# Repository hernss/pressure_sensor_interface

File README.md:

# Descripción del proyecto:

Se desea realizar un dispositivo que sirva de interface para un sensor analógico de presión. El sensor en cuestión es un sensor de presión absoluta que trabaja sobre una línea de aire comprimido, la salida de dicho sensor es del tipo 4-20mA y el rango te trabajo es de 0 a 10bar.
Este dispositivo tiene como objetivo mantener la línea de aire comprimido en un rango de presión predefinido por el usuario, y en caso de no encontrarse en dicho límite actúa como dispositivo de seguridad liberando la presión en la línea y haciendo sonar una alarma.
El núcleo de este proyecto es un Cortex M3 de la familia de STM el cual lleva implementado un sistema de control del estilo TDS el cual nos asegura el tiempo de respuesta en caso de presentarse una falla.
Por ser requerimiento de otra materia, se conectaron todos los periféricos a una línea de datos I2C. Estos periféricos son:

* Teclado Capacitivo (IQS316)
* Display LCD de 16 Caracteres 2 líneas con conversor I2C (PCF8754)
* Conversor Analógico Digital (ADS1115)
* Memoria EEPROM para parámetros de configuración (24LC16)
* Dos salidas a relé con optoacoplador de protección.

# Desarrollo en Kicad

Se optó por realizar dos PCB, uno para el teclado con el display y otro para el microcontrolador y los demás periféricos. Se desarrolló de esta manera ya que el teclado capacitivo necesitar ser implementado en el PCB y aplicado directamente sobre el panel frontal. Entonces, se hizo un PCB denominado PanelFrontal el cual lleva los pads del teclado capacitivo en la cara BOTTOM del PCB, se ubicaron los componentes en la cara TOP y se limitó el uso a solo componentes de montaje superficial, es así que al no tener componentes “through hole” no hay nada que sobresalga del lado BOTTOM y es así que el PCB puede ser apoyado directamente sobre el frente del gabinete. En el PCB denominado PlacaBase se implementó el micro-controlador y todos los periféricos ya que estos requieren varios componentes “through hole” y además de eso no hay una uniformidad de alturas lo cual complicaría el desarrollo en una sola placa junto al teclado.

# Calculo de los componentes:

## Fuente de Alimentación:
Nos vamos a encontrar con dos tipos de alimentación, el microcontrolador, la memoria EEPROM y el ADC se alimentan con 3,3V mientras que los demás dispositivos se alimentan con 5V. Es por esto que se decidió alimentar el dispositivo con una fuente externa de 5V DC 1A y se implementó en la placa base una fuente de alimentación de 3.3v basada en un LD1117 con sus respectivos capacitores.

## Capacitores de los cristales:
Para seleccionar estos capacitores vamos a referirnos a la hoja de datos de los cristales. Para el cristal de 8 MHz (ABM7-8.000MHZ-D2Y-T) vemos que la hoja de datos nos dice que capacitancia de carga es de 18 pF por ende se conectan dos capacitores de 18 pF en los pines del cristal a masa. Para el cristal de 32.768 KHz (ABS25-32.768KHZ-T) la hoja de datos nos dice que la capacitancia de carga es de 12.5 pF, en este caso se selecciona un capacitor de 12pF para conectar en los pines del cristal. Se diseña el circuito impreso de tal manera que ambas pistas que conectan al microcontrolador con el cristal tengan el mismo largo y la misma geometría.

## Leds internos de indicación:
Los leds se utilizaron los LTST-C171KRKT y LTST-C170KGKT ambos son excitados por una tensión de 3.3v ya que uno está conectado a una salida del microcontrolador y el otro directamente a los 3.3v de alimentación. Según la hoja de datos observamos que típicamente tienen 2v de tensión en directa. Se decidió usar una resistencia limitadora de 100 Ohms lo cual nos limitaría la corriente del diodo en 13 mA. Lo cual está por debajo de la corriente máxima de 30ma que acusa el fabricante.

I_F=(3.3v-2v)/(100 Ω)=13 mA

## Resistencias de los Optoacopladores:
Si nos referimos al datasheet de los optoacopladores PC817 vemos que la tensión en directa es de 1.2v mientras que la corriente es de 20 mA. En base a estos valores se calculó la resistencia limitadora.

R=(3.3v - 1.2v)/(20 mA)=105 Ω

Se adoptó una resistencia de 100 ohm siendo el valor comercial más cercano.

## Corriente de base en los transistores de los relés:
Se eligió los transistores BC846B para activar los relés. Estos transistores tienen una resistencia de base de 680 ohms. Si suponemos que los optoacopladores tiene la resistencia adecuada para su funcionamiento podemos calcular la corriente de base según la siguiente formula:

I_B=(5V- V_BE)/680Ω=(5V- 0.7v)/680Ω=6.3 mA

Teniendo en cuenta que el relé consume 80 mA, esta corriente nos asegura que el transistor se encuentra saturado con una tensión VCE menor a 0,2v

# Resistencia de entrada del ADC:
El sensor de presión con el que vamos a trabajar posee una salida de 4-20mA donde 4ma representa 0bar y 20mA 10bar. Es por esto que vamos a ajustar la resistencia para que esta corriente nos produzca una caída de tensión que podamos medir con el ADC. Se utilizó una resistencia de 100 ohms la cual se la eligió con una tolerancia de 0,1% ya que es fundamental que este valor de resistencia sea preciso ya que de ella depende la precisión de nuestra medición. Con este valor, la tensión en la entrada del ADC en el rango mínimo será de 0.4v y en el rango máximo de 2v. La tensión máxima admisible en la entrada del ADC es de 3.3v. Con esta configuración el ADC además de permitirnos medir el valor arrojado por el sensor nos da un margen como para medir si la entrada de corriente esta fuera de rango. El ADC tiene una resolución de 16bits, por ende tenemos una resolución de 3,3v / 2^16 = 50 µv/div, siendo para el rango mínimo de 0,4v / (50 µv/div) = 7943 y para el rango máximo 2v / (50 µv/div) = 39718

## Direcciones del Bus I2C:
Cada periférico tiene su propia dirección I2C para que todos puedan funcionar en el mismo bus. Estas especificaciones las obtenemos de las hojas de datos de los componentes. En general la mayoría tiene al menos un pin que podemos conectar a GND o Vcc para terminar de definir la dirección.
Para el caso de ADC el pin de configuración de dirección se conectó a GND asignándole una dirección “1001000x” (0x50h). En la memoria EEPROM los pines de dirección no se encuentran conectados ya que este tamaño de memoria no los implementa. La dirección I2C se usa en parte para direccionar internamente los bloques de memoria, es por esto que para la memoria se reservan las direcciones 0x60h hasta la 0x6Fh. El conversor I2C para el display LCD se le cablearon sus 3 pines de dirección a masa fijándole una dirección I2C de 0x70h. Para el integrado que controla el teclado capacitivo su pin de dirección se encuentra conectado a masa asignándole una dirección I2C de 0xE1h.
De esta manera, todos los periféricos nos quedan con direcciones distintas posibilitando la conexión al mismo bus I2C.

## Consumo total del Dispositivo:
Se analizaron los consumos máximos que podría llegar a tener el dispositivo así poder calcular la fuente de alimentación y el ancho de las pistas. Se analizaron solo los componentes más relevantes. Cada relé consume 80mA estando activados, el LCD tiene un consumo relevante el backligth que según la hoja de datos alcanza los 156 mA como máximo y podríamos sumarle algunos miliamperes mas por los demás componentes lo cual nos daría aproximadamente 330 mA sobre la línea de 5v.
 
# Diagrama Esquemático:

## Panel Frontal:

## Placa Base

# Circuito Impreso:

## Panel Frontal

## Placa Base

# Vista 3D de la placa terminada:

## Panel Frontal

## Placa Base

# Panelizado

# Gabinete

## Vista en 3D

# Link a ON-Shape:

https://cad.onshape.com/documents/e1ddf4852ee30d10dbbbdde3/w/8d886781dbbcdb7a099e42b0/e/7b9d0c14e845cfce50a3e853

# Links a Octopart:

## Panel Frontal:

https://octopart.com/bom-tool/DTLM5kml

## Placa Base:

https://octopart.com/bom-tool/Puk0rRIS

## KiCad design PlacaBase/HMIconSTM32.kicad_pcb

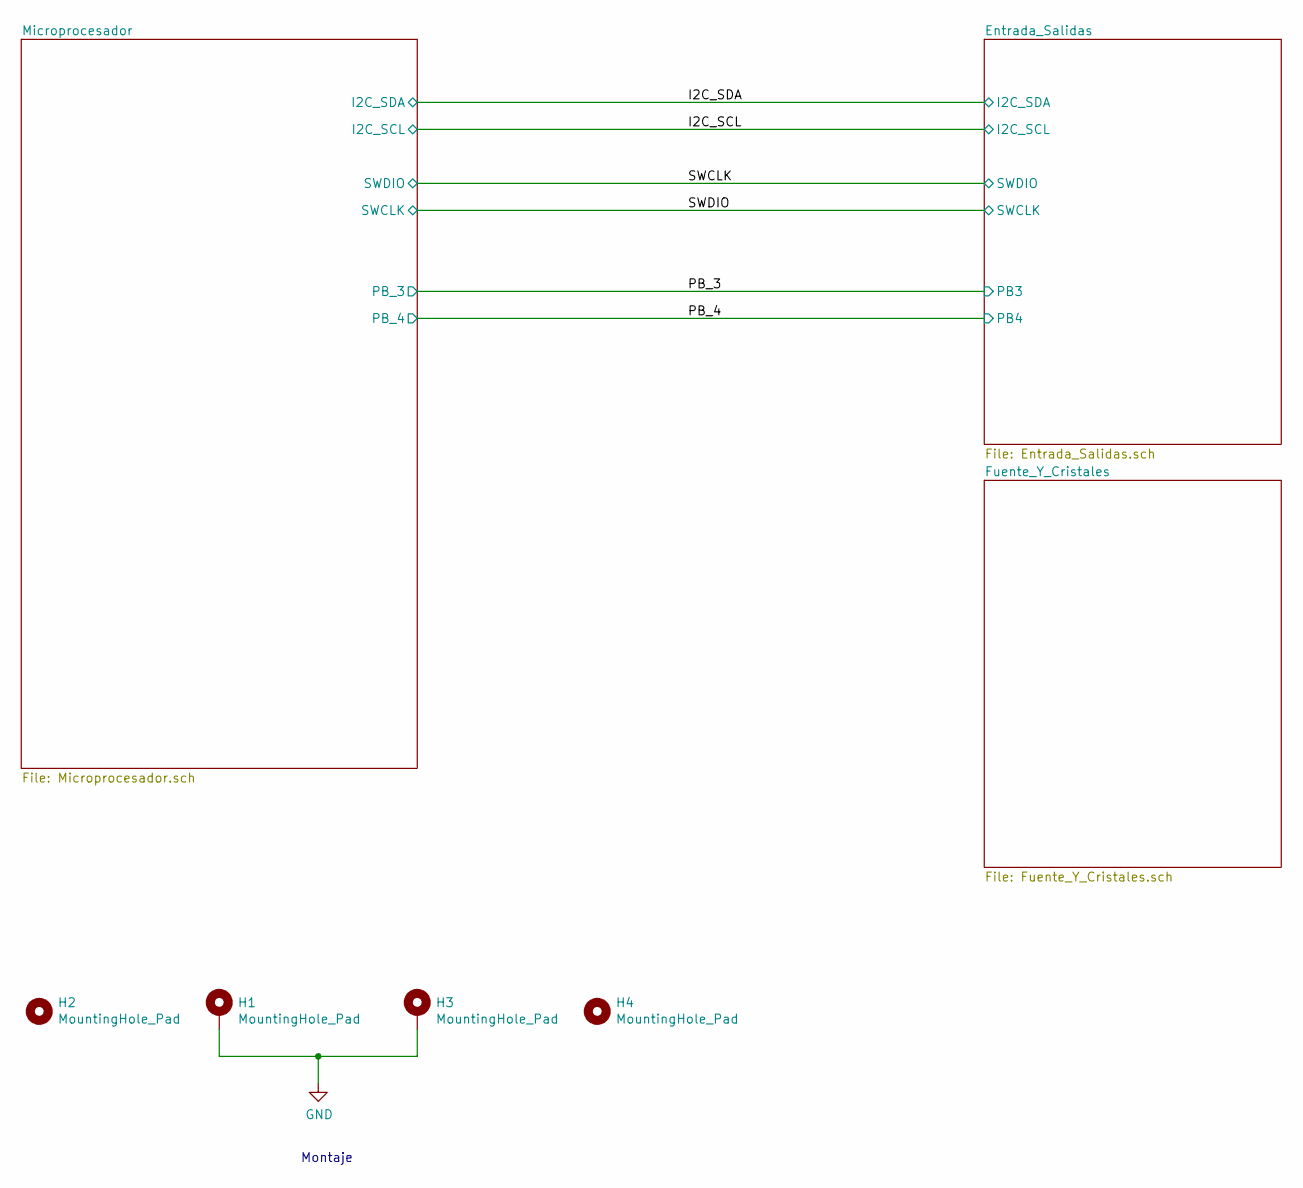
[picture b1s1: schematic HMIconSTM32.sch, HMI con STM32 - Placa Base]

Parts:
H1, H3: MountingHole_Pad; MountingHole_3.2mm_M3_Pad
H2, H4: MountingHole_Pad; MountingHole_3.2mm_M3

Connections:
GND: H1.1, H3.1; also elsewhere on the board

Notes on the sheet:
Montaje

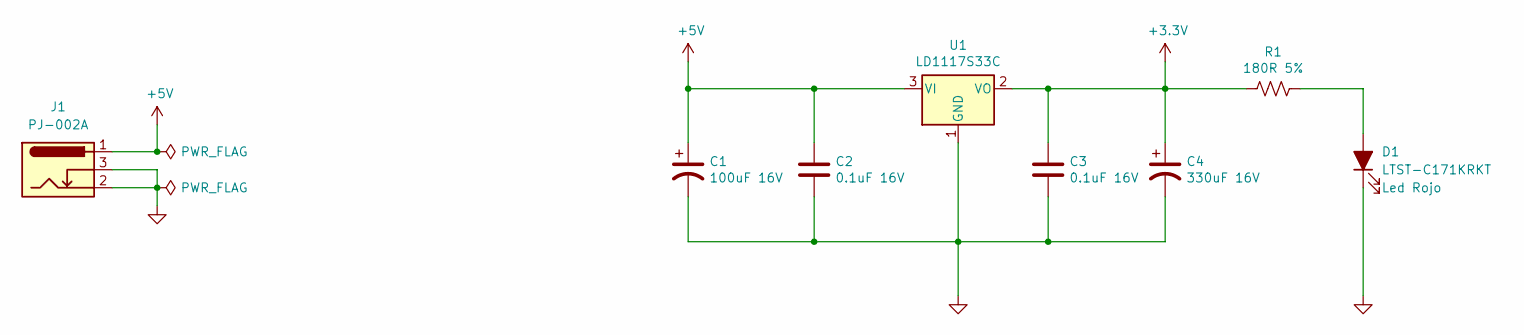
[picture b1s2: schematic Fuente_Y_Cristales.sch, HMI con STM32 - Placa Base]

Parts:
C1: 100uF 16V; CP_Elec_8x10.5; Manufacturer P/N EEE-HB1C101AP; Digikey P/N PCE4744CT-ND
C2, C3: 0.1uF 16V; C_0603_1608Metric; Manufacturer P/N CL10B104KO8NNNC; Digikey P/N 1276-1005-1-ND
C4: 330uF 16V; CP_Elec_10x10.5; Manufacturer P/N EEE-HB1C331AP; Digikey P/N PCE4748CT-ND
D1: LTST-C171KRKT; LED_0805_2012Metric; Manufacturer P/N LTST-C171KRKT; Digikey P/N 160-1427-2-ND
J1: PJ-002A; Manufacturer P/N PJ-002A; Digikey P/N CP-002A-ND
R1: 180R 5%; R_0603_1608Metric; Manufacturer P/N RC0603JR-07180RL; Digikey P/N 311-180GRCT-ND
U1: LD1117S33C; SOT-223-3_TabPin2; Manufacturer P/N LD1117S33CTR; Digikey P/N 497-1241-1-ND

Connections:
+3V3: C3.1, C4.1, R1.2, U1.2 (VO); also elsewhere on the board
+5V: C1.1, C2.1, J1.1, U1.3 (VI); also elsewhere on the board
GND: C1.2, C2.2, C3.2, C4.2, D1.1 (K), J1.2, J1.3, U1.1 (GND); also elsewhere on the board
unnamed: D1.2 (A), R1.1

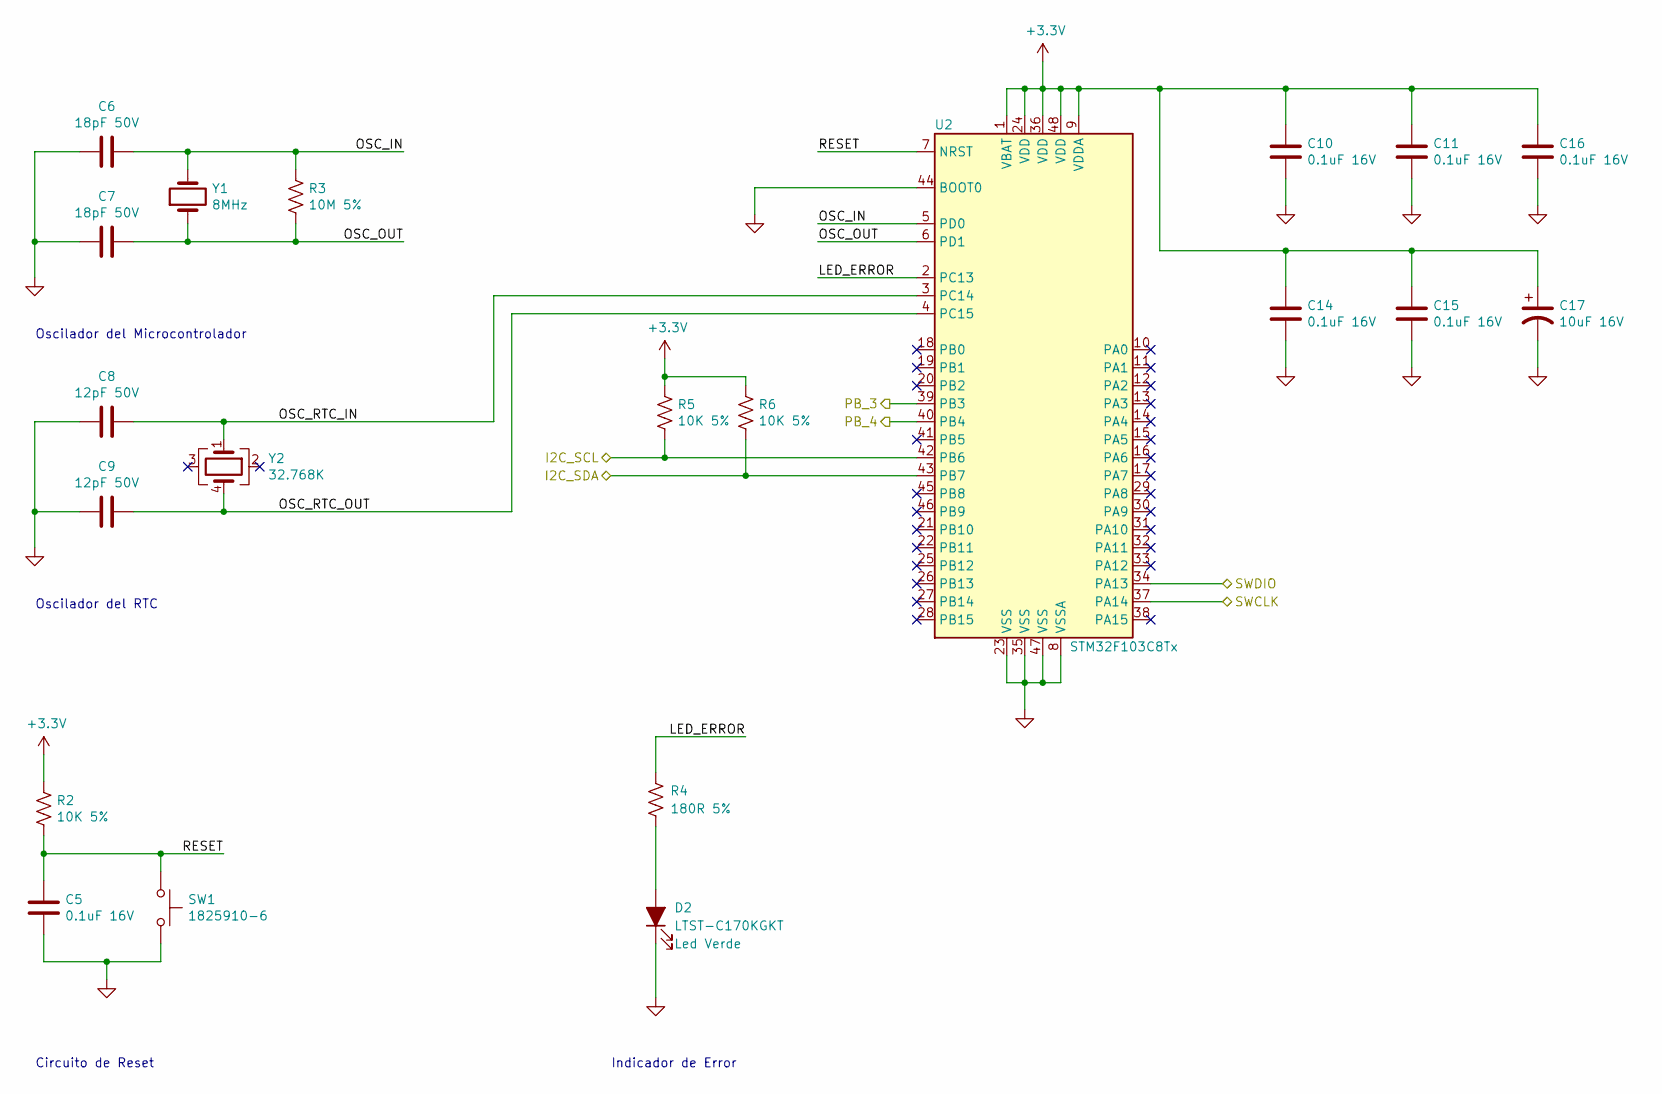
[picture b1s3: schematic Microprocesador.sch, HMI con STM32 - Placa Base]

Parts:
C5, C10, C11, C14, C15, C16: 0.1uF 16V; C_0603_1608Metric; Manufacturer P/N CL10B104KO8NNNC; Digikey P/N 1276-1005-1-ND
C6, C7: 18pF 50V; C_0603_1608Metric; Manufacturer P/N CL10C180JB8NNNC; Digikey P/N 1276-1089-1-ND
C8, C9: 12pF 50V; C_0603_1608Metric; Manufacturer P/N CL10C120JB8NNNC; Digikey P/N 1276-1254-1-ND
C17: 10uF 16V; CP_Elec_4x5.8; Manufacturer P/N EEE-HB1C100AR; Digikey P/N PCE4743CT-ND
D2: LTST-C170KGKT; LED_0805_2012Metric; Manufacturer P/N LTST-C170KGKT; Digikey P/N 160-1414-1-ND
R2, R5, R6: 10K 5%; R_0603_1608Metric; Manufacturer P/N AC0603JR-0710KL; Digikey P/N 311-10KLECT-ND
R3: 10M 5%; R_0603_1608Metric; Manufacturer P/N RC0603JR-0710ML; Digikey P/N 311-10MGRCT-ND
R4: 180R 5%; R_0603_1608Metric; Manufacturer P/N RC0603JR-07180RL; Digikey P/N 311-180GRCT-ND
SW1: 1825910-6; SW_PUSH_6mm_H5mm; Manufacturer P/N 1825910-6; Digikey P/N 450-1650-ND
U2: STM32F103C8Tx; LQFP-48_7x7mm_P0.5mm; Manufacturer P/N STM32F103C8T6TR; Digikey P/N 497-17666-1-ND
Y1: 8MHz; Crystal_SMD_Abracon_ABM7-2Pin_6.0x3.5mm; Manufacturer P/N ABM7-8.000MHZ-D2Y-T; Digikey P/N 535-9831-1-ND
Y2: 32.768K; Crystal_SMD_Abracon_ABS25-4Pin_8.0x3.8mm; Manufacturer P/N ABS25-32.768KHZ-T; Digikey P/N 535-9166-1-ND

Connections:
+3V3: C10.1, C11.1, C14.1, C15.1, C16.1, C17.1, R2.1, R5.1, R6.1, U2.1 (VBAT), U2.9 (VDDA), U2.24 (VDD), U2.36 (VDD), U2.48 (VDD); also elsewhere on the board
/I2C_SCL: R5.2, U2.42 (PB6); also elsewhere on the board
/I2C_SDA: R6.2, U2.43 (PB7); also elsewhere on the board
/Microprocesador/LED_ERROR: R4.2, U2.2 (PC13)
/Microprocesador/OSC_IN: C6.2, R3.1, U2.5 (PD0), Y1.2
/Microprocesador/OSC_OUT: C7.2, R3.2, U2.6 (PD1), Y1.1
/Microprocesador/OSC_RTC_IN: C8.2, U2.3 (PC14), Y2.1
/Microprocesador/OSC_RTC_OUT: C9.2, U2.4 (PC15), Y2.4
/Microprocesador/RESET: C5.1, R2.2, SW1.1, U2.7 (NRST)
/PB_3: U2.39 (PB3); also elsewhere on the board
/PB_4: U2.40 (PB4); also elsewhere on the board
/SWCLK: U2.34 (PA13); also elsewhere on the board
/SWDIO: U2.37 (PA14); also elsewhere on the board
GND: C5.2, C6.1, C7.1, C8.1, C9.1, C10.2, C11.2, C14.2, C15.2, C16.2, C17.2, D2.1 (K), SW1.2, U2.8 (VSSA), U2.23 (VSS), U2.35 (VSS), U2.44 (BOOT0), U2.47 (VSS); also elsewhere on the board
unnamed: D2.2 (A), R4.1

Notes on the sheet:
Circuito de Reset
Oscilador del RTC
Oscilador del Microcontrolador
Indicador de Error

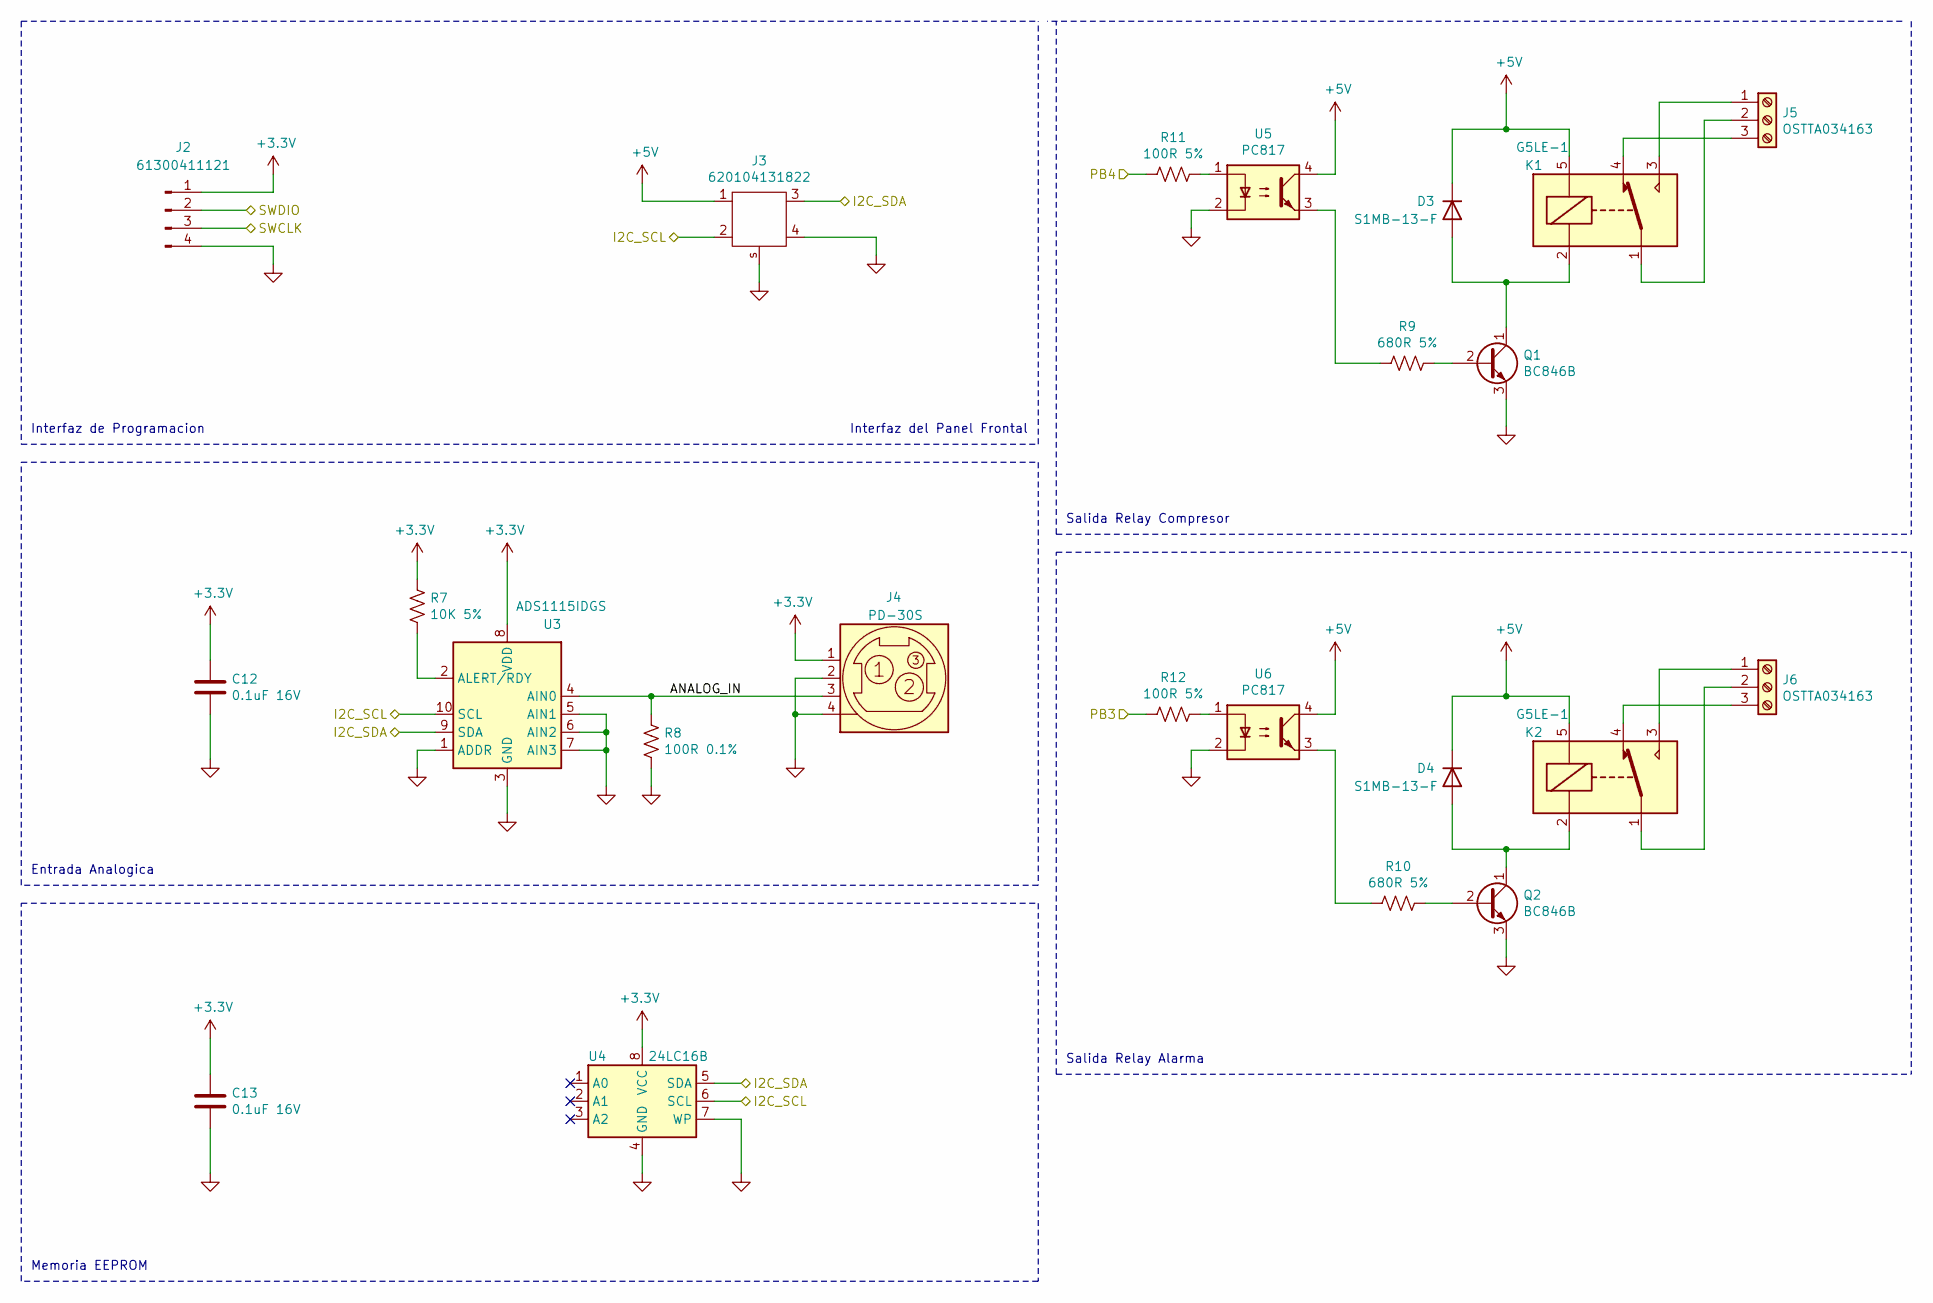
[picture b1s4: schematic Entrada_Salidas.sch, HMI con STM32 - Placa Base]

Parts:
C12, C13: 0.1uF 16V; C_0603_1608Metric; Manufacturer P/N CL10B104KO8NNNC; Digikey P/N 1276-1005-1-ND
D3, D4: S1MB-13-F; D_SMB; Manufacturer P/N S1MB-13-F; Digikey P/N S1MB-FDICT-ND
J2: 61300411121; PinHeader_1x04_P2.54mm_Vertical; Manufacturer P/N 61300411121; Digikey P/N 732-5317-ND
J3: 620104131822; Manufacturer P/N 620104131822; Digikey P/N 732-2713-1-ND
J4: PD-30S; CUI_PD-30S; Manufacturer P/N PD-30S; Digikey P/N CP-7230-ND
J5, J6: OSTTA034163; Manufacturer P/N OSTTA034163; Digikey P/N ED2581-ND
K1, K2: G5LE-1; Relay_SPDT_Omron-G5LE-1; Manufacturer P/N G5LE-14 DC5; Digikey P/N Z1011-ND
Q1, Q2: BC846B; SOT-23; Manufacturer P/N BC846BLT3G; Digikey P/N BC846BLT3GOSCT-ND
R7: 10K 5%; R_0603_1608Metric; Manufacturer P/N AC0603JR-0710KL; Digikey P/N 311-10KLECT-ND
R8: 100R 0.1%; R_0603_1608Metric; Manufacturer P/N RT0603BRD07100RL; Digikey P/N YAG1497DKR-ND
R9, R10: 680R 5%; R_0603_1608Metric; Manufacturer P/N RC0603JR-07680RL; Digikey P/N 311-680GRCT-ND
R11, R12: 100R 5%; R_0603_1608Metric; Manufacturer P/N RC0603JR-07100RL; Digikey P/N 311-100GRCT-ND
U3: ADS1115IDGS; TSSOP-10_3x3mm_P0.5mm; Manufacturer P/N ADS1115IDGSR; Digikey P/N 296-38849-1-ND
U4: 24LC16B; SOIC-8_3.9x4.9mm_P1.27mm; Manufacturer P/N 24LC16BT-I/SN; Digikey P/N 24LC16BT-I/SNCT-ND
U5, U6: PC817; DIP-4_W7.62mm; Manufacturer P/N PC81710NIP1B; Digikey P/N 1855-1014-1-ND

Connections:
+3V3: C12.1, C13.1, J2.1, J4.1, R7.2, U3.8 (VDD), U4.8 (VCC); also elsewhere on the board
+5V: D3.1 (K), D4.1 (K), J3.1, K1.5, K2.5, U5.4, U6.4; also elsewhere on the board
/Entrada_Salidas/ANALOG_IN: J4.3, R8.2, U3.4 (AIN0)
/I2C_SCL: J3.2, U3.10 (SCL), U4.6 (SCL); also elsewhere on the board
/I2C_SDA: J3.3, U3.9 (SDA), U4.5 (SDA); also elsewhere on the board
/PB_3: R12.1; also elsewhere on the board
/PB_4: R11.1; also elsewhere on the board
/SWCLK: J2.2; also elsewhere on the board
/SWDIO: J2.3; also elsewhere on the board
GND: C12.2, C13.2, J2.4, J3.4, J3.s, J4.2, J4.4 (Shield), Q1.3 (E), Q2.3 (E), R8.1, U3.1 (ADDR), U3.3 (GND), U3.5 (AIN1), U3.6 (AIN2), U3.7 (AIN3), U4.4 (GND), U4.7 (WP), U5.2, U6.2; also elsewhere on the board
unnamed: D3.2 (A), K1.2, Q1.1 (C)
unnamed: D4.2 (A), K2.2, Q2.1 (C)
unnamed: J5.1, K1.3
unnamed: J5.2, K1.1
unnamed: J5.3, K1.4
unnamed: J6.1, K2.3
unnamed: J6.2, K2.1
unnamed: J6.3, K2.4
unnamed: Q1.2 (B), R9.2
unnamed: Q2.2 (B), R10.2
unnamed: R7.1, U3.2 (ALERT/RDY)
unnamed: R9.1, U5.3
unnamed: R10.1, U6.3
unnamed: R11.2, U5.1
unnamed: R12.2, U6.1

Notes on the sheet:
Salida Relay Compresor
Salida Relay Alarma
Interfaz de Programacion
Interfaz del Panel Frontal
Entrada Analogica
Memoria EEPROM

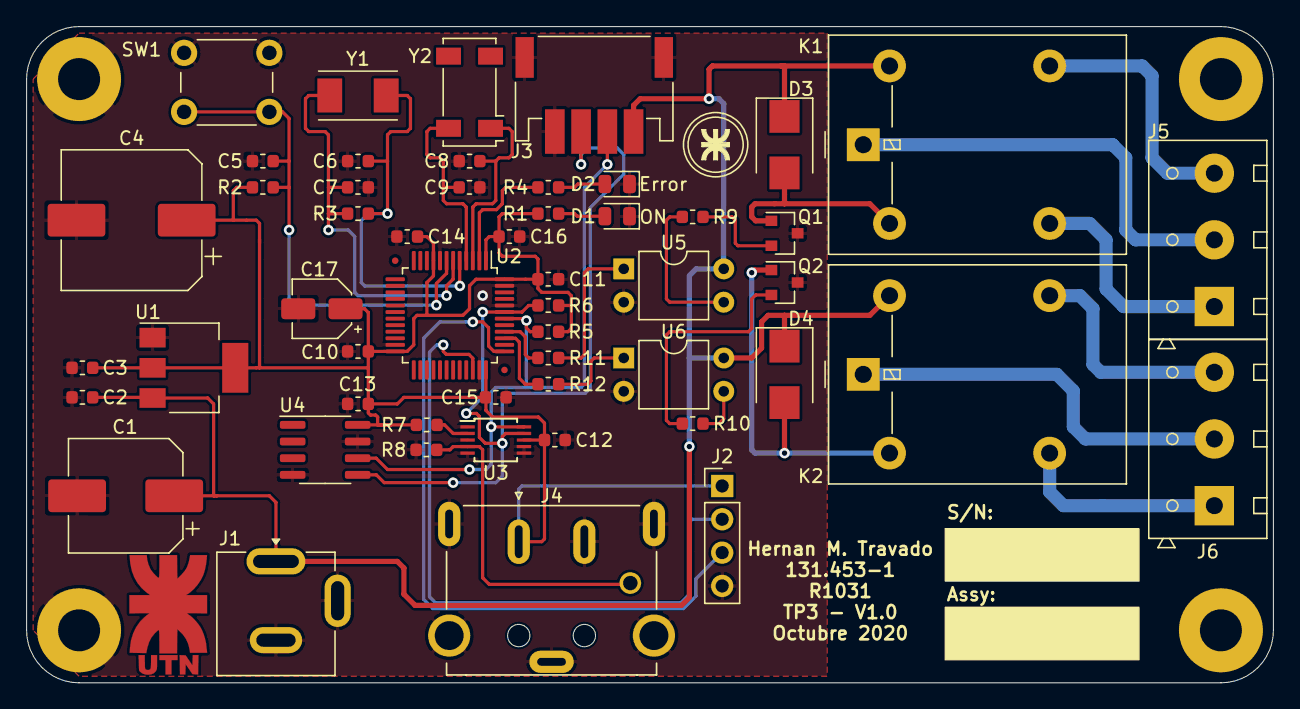
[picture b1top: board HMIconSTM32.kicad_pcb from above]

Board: 2 copper layers, 95.0 x 50.0 mm, 57 parts (0 on the bottom side), 33 nets.

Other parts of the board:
LogoUTN.BA: UTN.BA

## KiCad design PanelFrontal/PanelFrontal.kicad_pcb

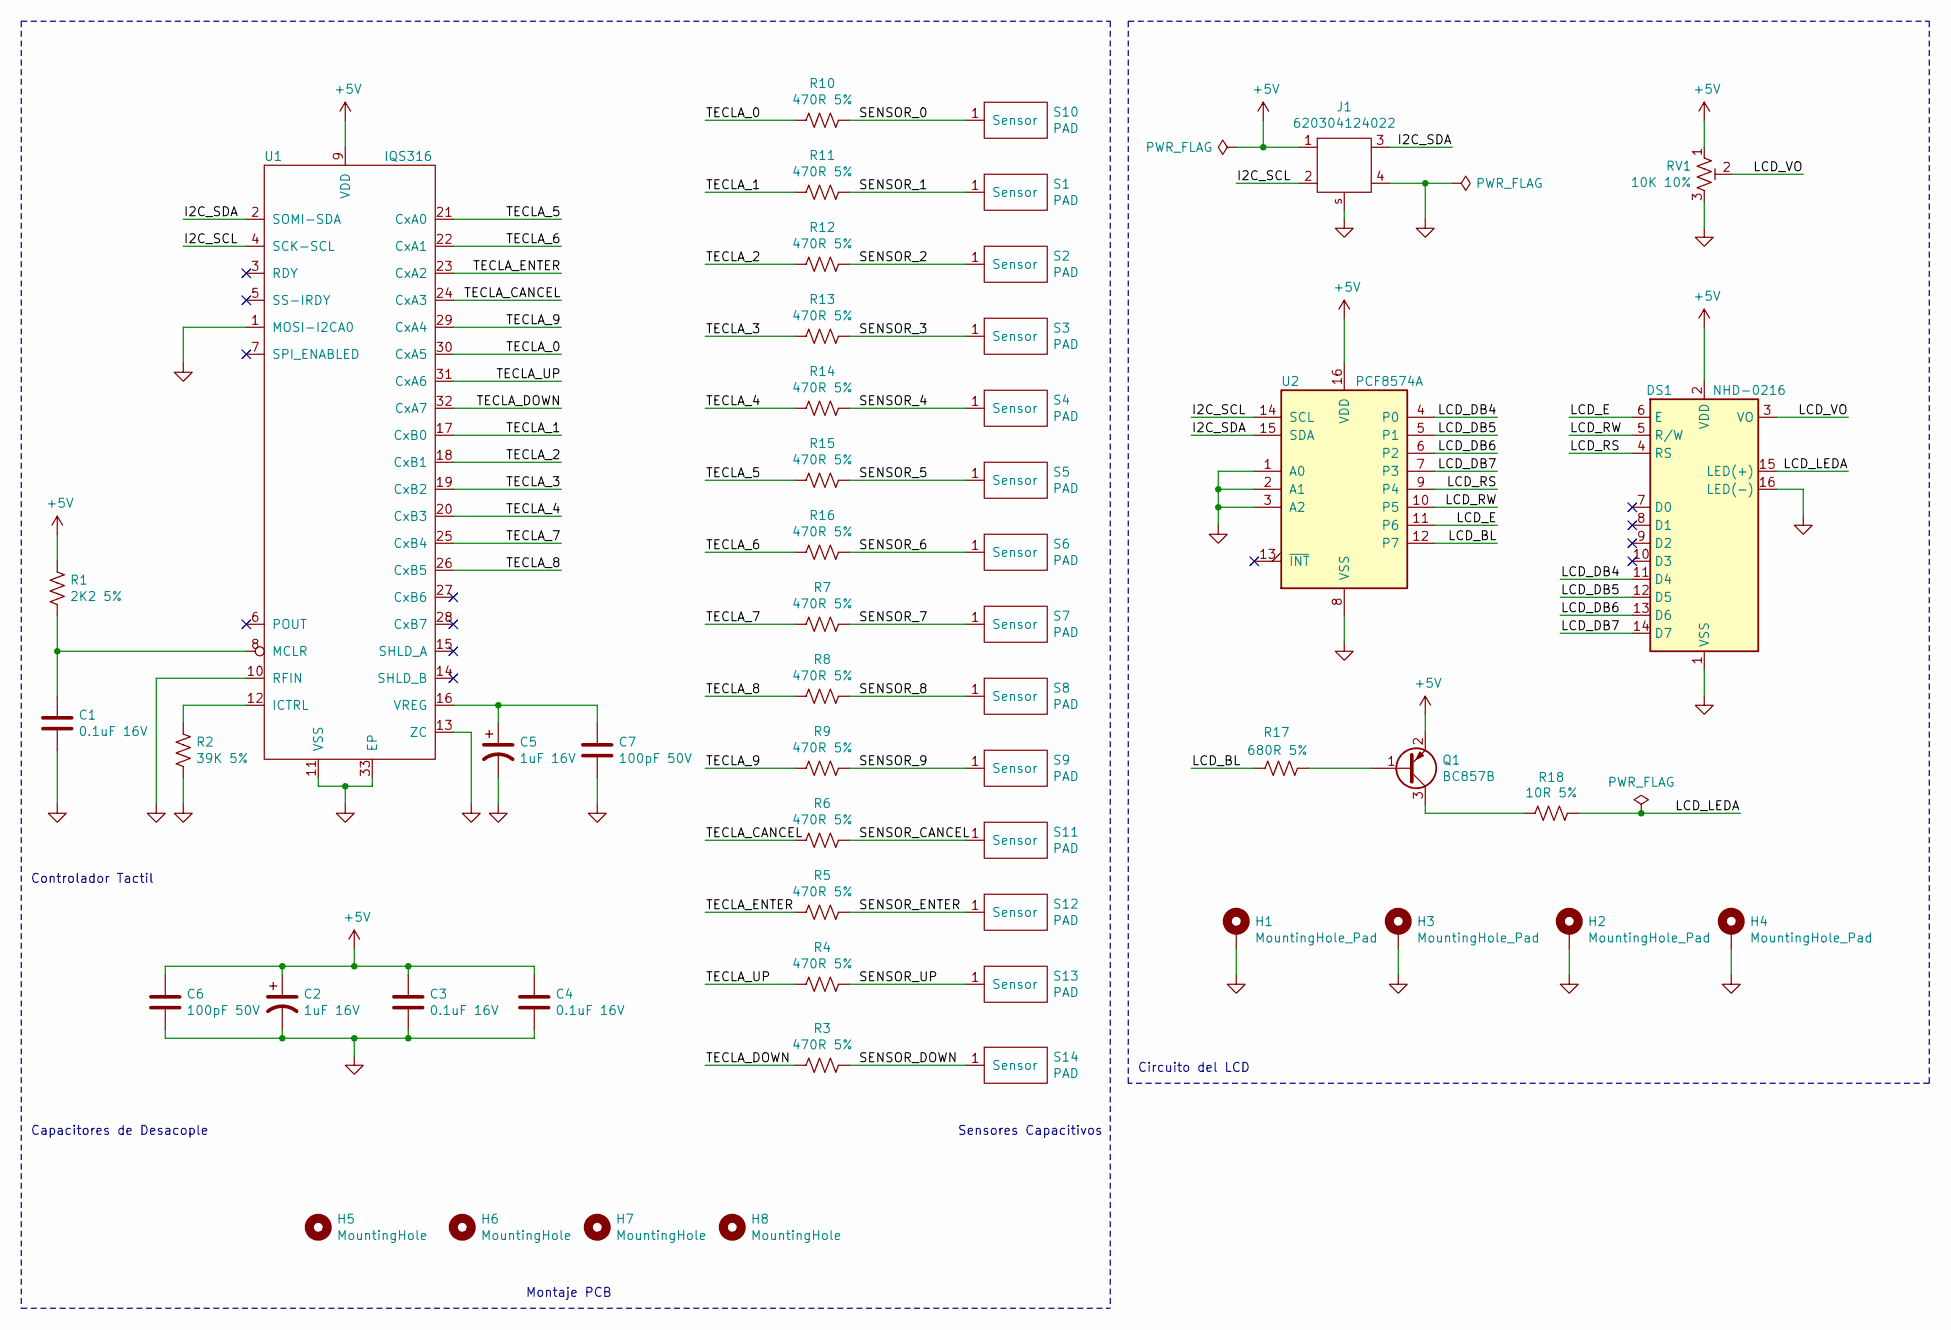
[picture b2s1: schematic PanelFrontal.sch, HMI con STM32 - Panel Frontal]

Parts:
C1, C3, C4: 0.1uF 16V; C_0603_1608Metric; Manufacturer P/N CL10B104KO8NNNC; Digikey P/N 1276-1005-1-ND
C2, C5: 1uF 16V; CP_Elec_4x5.4; Manufacturer P/N EEE-FC1V1R0R; Digikey P/N PCE4024CT-ND
C6, C7: 100pF 50V; C_0603_1608Metric; Manufacturer P/N CL10C101JB8NNNC; Digikey P/N 1276-1008-1-ND
DS1: NHD-0216; Manufacturer P/N NHD-0216K1Z-FL-YBW; Digikey P/N NHD-0216K1Z-FL-YBW-ND
H1, H2, H3, H4: MountingHole_Pad; 9774070243R; Manufacturer P/N 9774070243R; Digikey P/N 732-7107-1-ND
H5, H6, H7, H8: MountingHole; MountingHole_3.2mm_M3
J1: 620304124022; Manufacturer P/N 620304124022; Digikey P/N 732-2709-1-ND
Q1: BC857B; SOT-23; Manufacturer P/N BC857BLT1G; Digikey P/N BC857BLT1GOSCT-ND
R1: 2K2 5%; R_0603_1608Metric; Manufacturer P/N RC0603JR-072K2L; Digikey P/N 311-2.2KGRCT-ND
R2: 39K 5%; R_0603_1608Metric; Manufacturer P/N RC0603JR-0739KL; Digikey P/N 311-39KGRCT-ND
R3, R4, R5, R6, R7, R8, R9, R10, R11, R12, R13, R14, R15, R16: 470R 5%; R_0603_1608Metric; Manufacturer P/N RC0603JR-07100RL; Digikey P/N 311-100GRCT-ND
R17: 680R 5%; R_0603_1608Metric; Manufacturer P/N RC0603JR-07680RL; Digikey P/N 311-680GRCT-ND
R18: 10R 5%; R_0603_1608Metric; Manufacturer P/N RC0603JR-0710RL; Digikey P/N 311-10GRCT-ND
RV1: 10K 10%; 3361P-1-XXXGLF; Manufacturer P/N 3361P-1-103GLF; Digikey P/N 3361P-103GLFCT-ND
S1, S2, S3, S4, S5, S6, S7, S8, S9, S10, S11, S12, S13, S14: PAD; TouchSensor
U1: IQS316; QFN-32-1EP_5x5mm_P0.5mm_EP3.65x3.65mm; Manufacturer P/N IQS316-0-QFR; Digikey P/N 1790-1042-1-ND
U2: PCF8574A; SOIC-16W_7.5x10.3mm_P1.27mm; Manufacturer P/N PCF8574AT/3,518; Digikey P/N 568-1074-1-ND

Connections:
+5V: C2.1, C3.1, C4.1, C6.1, DS1.2 (VDD), J1.1, Q1.2 (E), R1.1, RV1.1, U1.9 (VDD), U2.16 (VDD)
/I2C_SCL: J1.2, U1.4 (SCK-SCL), U2.14 (SCL)
/I2C_SDA: J1.3, U1.2 (SOMI-SDA), U2.15 (SDA)
/LCD_BL: R17.1, U2.12 (P7)
/LCD_DB4: DS1.11 (D4), U2.4 (P0)
/LCD_DB5: DS1.12 (D5), U2.5 (P1)
/LCD_DB6: DS1.13 (D6), U2.6 (P2)
/LCD_DB7: DS1.14 (D7), U2.7 (P3)
/LCD_E: DS1.6 (E), U2.11 (P6)
/LCD_LEDA: DS1.15 (LED(+)), R18.1
/LCD_RS: DS1.4 (RS), U2.9 (P4)
/LCD_RW: DS1.5 (R/W), U2.10 (P5)
/LCD_VO: DS1.3 (VO), RV1.2
/SENSOR_0: R10.1, S10.1
/SENSOR_1: R11.1, S1.1
/SENSOR_2: R12.1, S2.1
/SENSOR_3: R13.1, S3.1
/SENSOR_4: R14.1, S4.1
/SENSOR_5: R15.1, S5.1
/SENSOR_6: R16.1, S6.1
/SENSOR_7: R7.1, S7.1
/SENSOR_8: R8.1, S8.1
/SENSOR_9: R9.1, S9.1
/SENSOR_CANCEL: R6.1, S11.1
/SENSOR_DOWN: R3.1, S14.1
/SENSOR_ENTER: R5.1, S12.1
/SENSOR_UP: R4.1, S13.1
/TECLA_0: R10.2, U1.30 (CxA5)
/TECLA_1: R11.2, U1.17 (CxB0)
/TECLA_2: R12.2, U1.18 (CxB1)
/TECLA_3: R13.2, U1.19 (CxB2)
/TECLA_4: R14.2, U1.20 (CxB3)
/TECLA_5: R15.2, U1.21 (CxA0)
/TECLA_6: R16.2, U1.22 (CxA1)
/TECLA_7: R7.2, U1.25 (CxB4)
/TECLA_8: R8.2, U1.26 (CxB5)
/TECLA_9: R9.2, U1.29 (CxA4)
/TECLA_CANCEL: R6.2, U1.24 (CxA3)
/TECLA_DOWN: R3.2, U1.32 (CxA7)
/TECLA_ENTER: R5.2, U1.23 (CxA2)
/TECLA_UP: R4.2, U1.31 (CxA6)
GND: C1.2, C2.2, C3.2, C4.2, C5.2, C6.2, C7.2, DS1.1 (VSS), DS1.16 (LED(-)), H1.1, H2.1, H3.1, H4.1, J1.4, J1.s, R2.2, RV1.3, U1.1 (MOSI-I2CA0), U1.10 (RFIN), U1.11 (VSS), U1.13 (ZC), U1.33 (EP), U2.1 (A0), U2.2 (A1), U2.3 (A2), U2.8 (VSS)
unnamed: C1.1, R1.2, U1.8 (MCLR)
unnamed: C5.1, C7.1, U1.16 (VREG)
unnamed: Q1.1 (B), R17.2
unnamed: Q1.3 (C), R18.2
unnamed: R2.1, U1.12 (ICTRL)

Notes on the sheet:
Circuito del LCD
Controlador Tactil
Capacitores de Desacople
Sensores Capacitivos
Montaje PCB

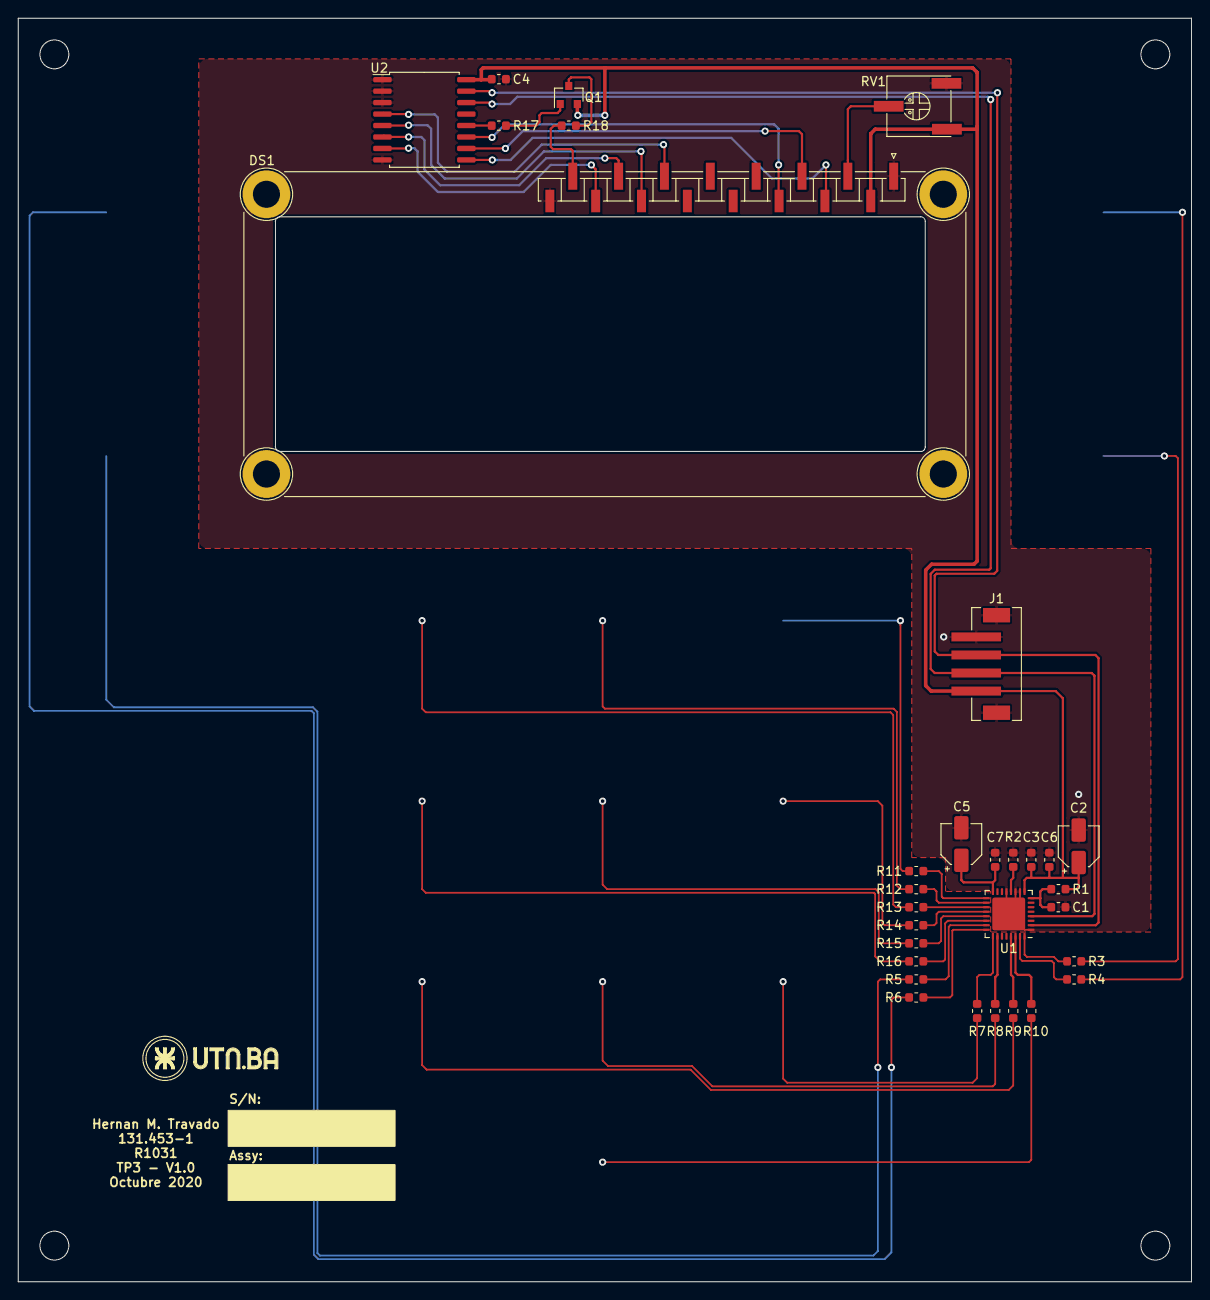
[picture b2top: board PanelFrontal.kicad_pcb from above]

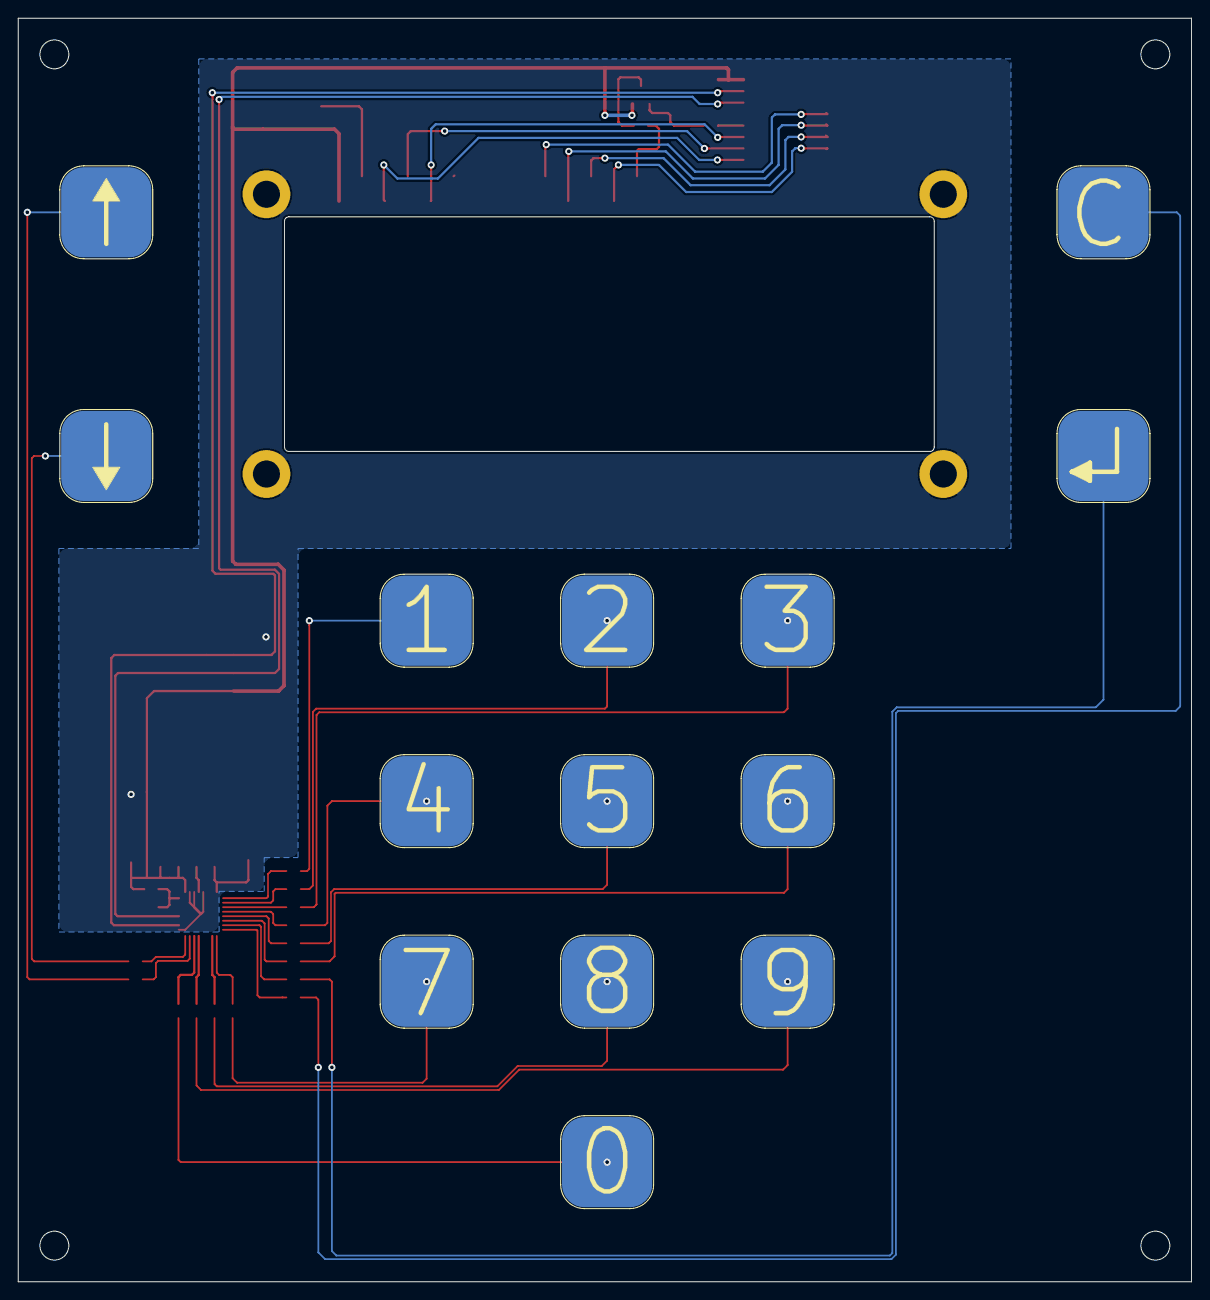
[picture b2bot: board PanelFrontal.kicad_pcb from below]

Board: 2 copper layers, 130.0 x 140.0 mm, 54 parts (14 on the bottom side), 47 nets.

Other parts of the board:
LogoUTN.BA-Letras: UTN.BA-Letras

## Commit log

2023-02-13 README Update
